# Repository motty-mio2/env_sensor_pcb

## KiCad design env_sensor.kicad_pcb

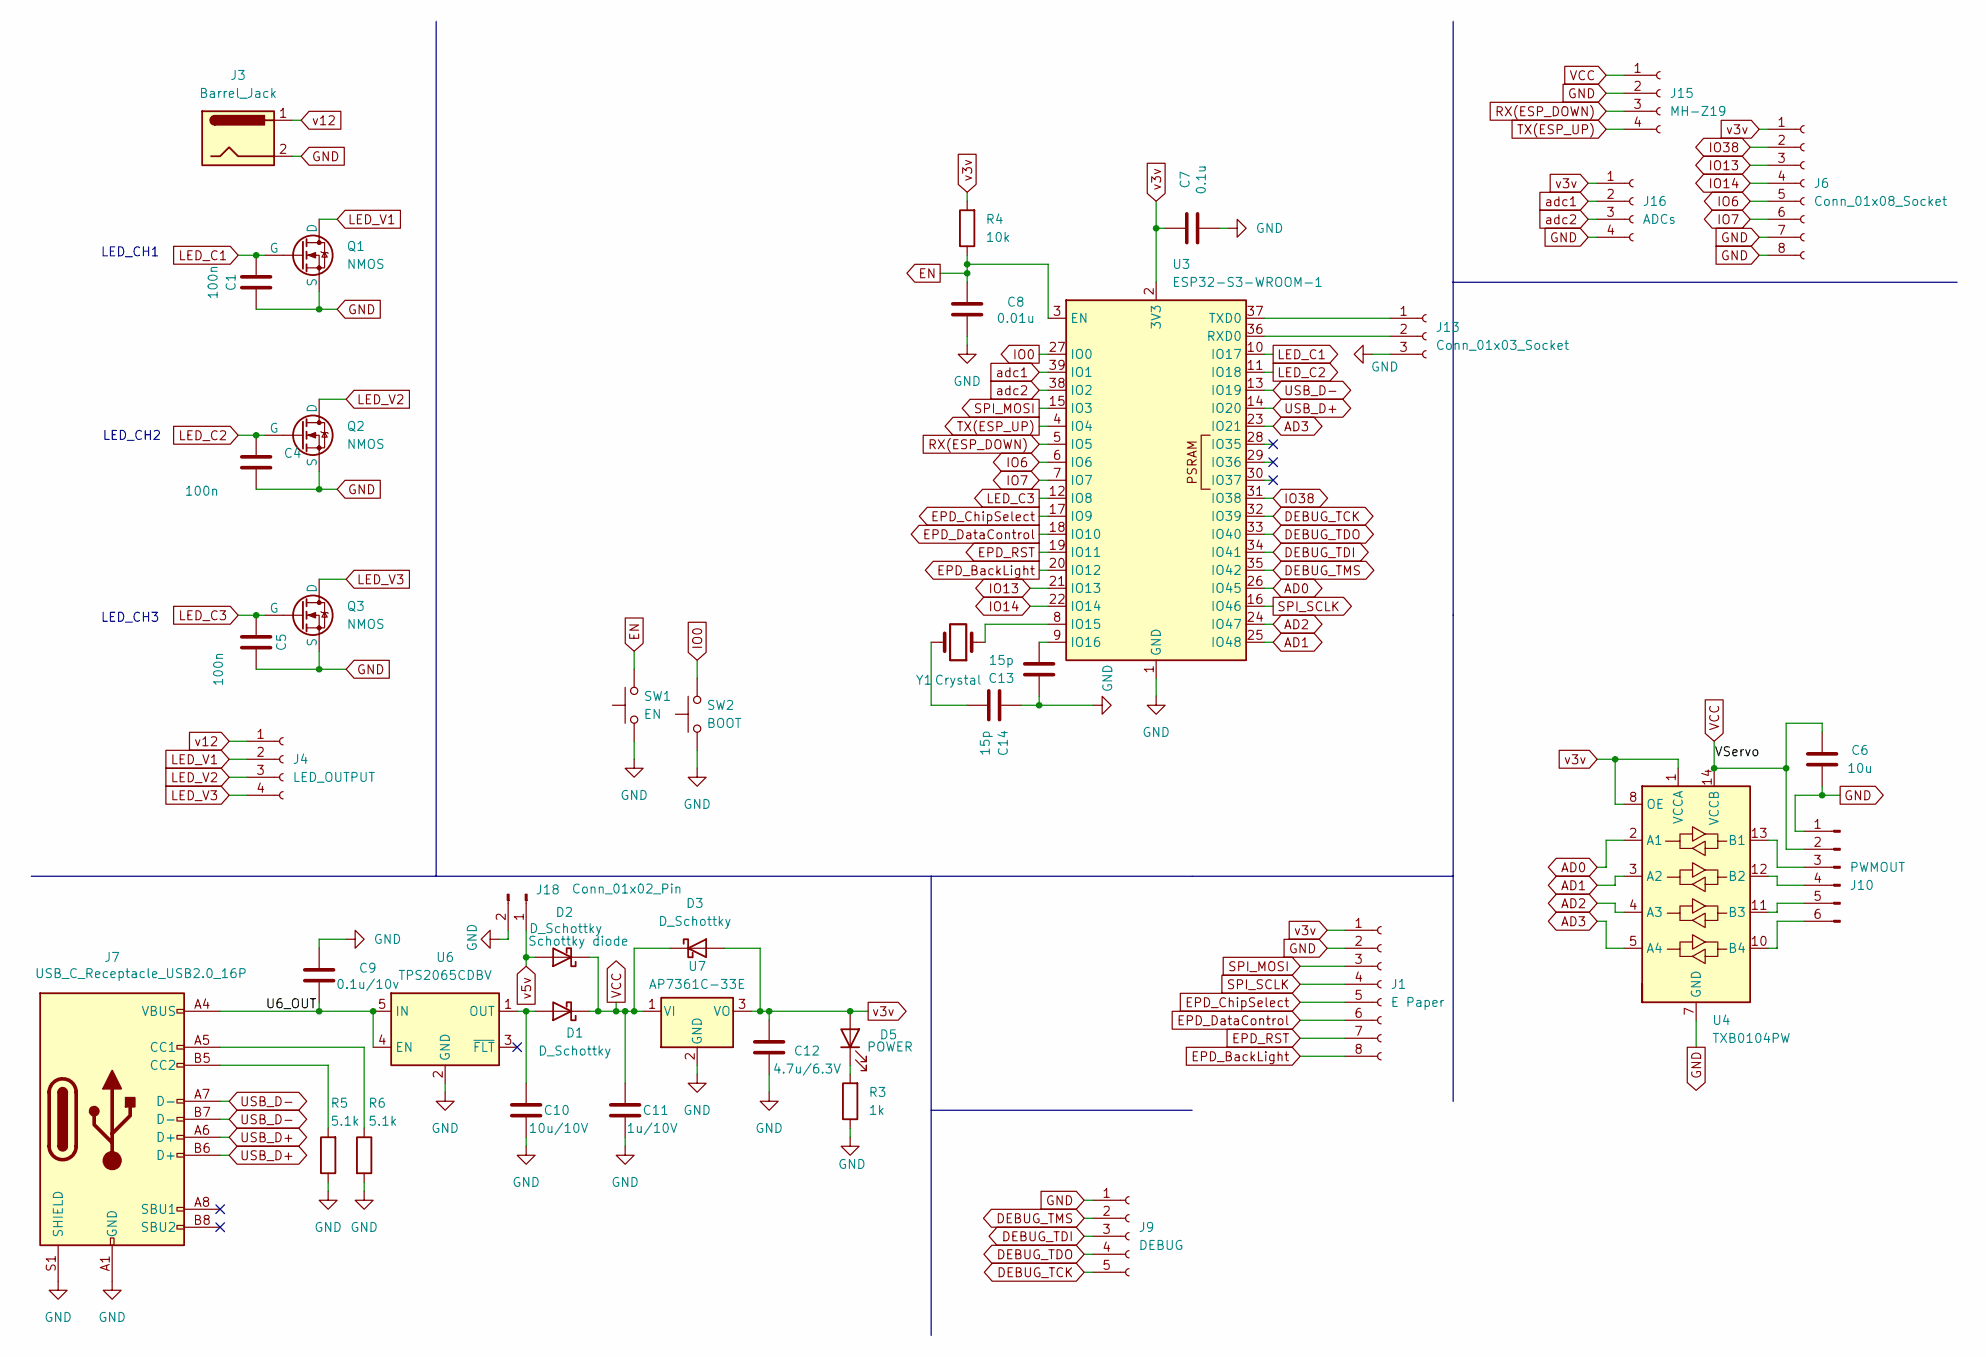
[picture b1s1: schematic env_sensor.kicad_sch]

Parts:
C1, C4, C5: 100n; C_0603_1608Metric; LCSC C14663
C6: 10u; C_0603_1608Metric; LCSC C19702
C7: 0.1u; C_0603_1608Metric; LCSC C14663
C8: 0.01u; C_0603_1608Metric; LCSC C57112
C9: 0.1u/10v; C_0603_1608Metric; LCSC C14663
C10: 10u/10V; C_0603_1608Metric; LCSC C19702
C11: 1u/10V; C_0603_1608Metric; LCSC C15849
C12: 4.7u/6.3V; C_0603_1608Metric; LCSC C19666
C13, C14: 15p; C_0603_1608Metric; LCSC C1644
D1, D2, D3: D_Schottky; D_SMA; LCSC C123070
D5: POWER; LED_0603_1608Metric; LCSC C2286
J1: E Paper; PinSocket_1x08_P2.54mm_Vertical
J3: Barrel_Jack; BarrelJack_GCT_DCJ200-10-A_Horizontal
J4: LED_OUTPUT; PinHeader_1x04_P2.54mm_Vertical
J6: Conn_01x08_Socket; PinSocket_2x04_P2.54mm_Vertical
J7: USB_C_Receptacle_USB2.0_16P; USB_C_Receptacle_GCT_USB4085; LCSC C7095263
J9: DEBUG; PinHeader_1x05_P2.54mm_Vertical
J10: PWMOUT; PinHeader_1x06_P2.54mm_Vertical
J13: Conn_01x03_Socket; PinHeader_1x03_P2.54mm_Vertical
J15: MH-Z19; PinSocket_1x04_P2.54mm_Vertical
J16: ADCs; PinSocket_1x04_P2.54mm_Vertical
J18: Conn_01x02_Pin; PinHeader_1x02_P2.54mm_Vertical
Q1, Q2, Q3: NMOS; TO-252; LCSC C557932
R3: 1k; R_0603_1608Metric; LCSC C21190
R4: 10k; R_0603_1608Metric; LCSC C25804
R5, R6: 5.1k; R_0603_1608Metric; LCSC C23186
SW1: EN; TVAF06-A020B-R; LCSC C2844396
SW2: BOOT; TVAF06-A020B-R; LCSC C2844396
U3: ESP32-S3-WROOM-1
U4: TXB0104PW; TSSOP-14_4.4x5mm_P0.65mm; LCSC C60708
U6: TPS2065CDBV; SOT-23-5; LCSC C353882
U7: AP7361C-33E; SOT-223-3_TabPin2; LCSC C500795
Y1: Crystal; Crystal_SMD_3215-2Pin_3.2x1.5mm; LCSC C1669858

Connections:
/U6_OUT: C9.2, J7.A4 (VBUS), J7.A9 (VBUS), J7.B4 (VBUS), J7.B9 (VBUS), U6.4 (EN), U6.5 (IN)
AD0: U3.26 (IO45), U4.2 (A1)
AD1: U3.25 (IO48), U4.3 (A2)
AD2: U3.24 (IO47), U4.4 (A3)
AD3: U3.23 (IO21), U4.5 (A4)
DEBUG_TCK: J9.5, U3.32 (IO39)
DEBUG_TDI: J9.3, U3.34 (IO41)
DEBUG_TDO: J9.4, U3.33 (IO40)
DEBUG_TMS: J9.2, U3.35 (IO42)
EN: C8.1, R4.1, SW1.2, U3.3 (EN)
EPD_BackLight: J1.8, U3.20 (IO12)
EPD_ChipSelect: J1.5, U3.17 (IO9)
EPD_DataControl: J1.6, U3.18 (IO10)
EPD_RST: J1.7, U3.19 (IO11)
GND: C1.2, C4.1, C5.1, C6.2, C7.2, C8.2, C9.1, C10.2, C11.2, C12.2, C13.1, C14.1, J1.2, J3.2, J6.7, J6.8, J7.A1 (GND), J7.A12 (GND), J7.B1 (GND), J7.B12 (GND), J7.S1 (SHIELD), J9.1, J10.1, J13.3, J15.2, J16.4, J18.2, Q1.3 (S), Q2.3 (S), Q3.3 (S), R3.1, R5.1, R6.2, SW1.1, SW2.1, U3.1 (GND), U3.40 (GND), U3.41 (GND), U4.7 (GND), U6.2 (GND), U7.2 (GND)
IO0: SW2.2, U3.27 (IO0)
IO6: J6.5, U3.6 (IO6)
IO7: J6.6, U3.7 (IO7)
IO13: J6.3, U3.21 (IO13)
IO14: J6.4, U3.22 (IO14)
IO38: J6.2, U3.31 (IO38)
LED_C1: C1.1, Q1.2 (G), U3.10 (IO17)
LED_C2: C4.2, Q2.2 (G), U3.11 (IO18)
LED_C3: C5.2, Q3.2 (G), U3.12 (IO8)
LED_V1: J4.2, Q1.1 (D)
LED_V2: J4.3, Q2.1 (D)
LED_V3: J4.4, Q3.1 (D)
unnamed: C14.2, Y1.2
unnamed: C10.1, D1.2 (A), U6.1 (OUT)
unnamed: D5.1 (K), R3.2
unnamed: J7.A5 (CC1), R6.1
unnamed: J7.B5 (CC2), R5.2
unnamed: J10.3, U4.13 (B1)
unnamed: J10.4, U4.12 (B2)
unnamed: J10.5, U4.11 (B3)
unnamed: J10.6, U4.10 (B4)
unnamed: J13.1, U3.37 (TXD0)
unnamed: J13.2, U3.36 (RXD0)
unnamed: U3.8 (IO15), Y1.1
unnamed: C13.2, U3.9 (IO16)
RX(ESP_DOWN): J15.3, U3.5 (IO5)
SPI_MOSI: J1.3, U3.15 (IO3)
SPI_SCLK: J1.4, U3.16 (IO46)
TX(ESP_UP): J15.4, U3.4 (IO4)
USB_D+: J7.A6 (D+), J7.B6 (D+), U3.14 (IO20)
USB_D-: J7.A7 (D-), J7.B7 (D-), U3.13 (IO19)
VCC: C6.1, C11.1, D1.1 (K), D2.1 (K), D3.1 (K), J10.2, J15.1, U4.14 (VCCB), U7.1 (VI)
adc1: J16.2, U3.39 (IO1)
adc2: J16.3, U3.38 (IO2)
v3v: C7.1, C12.1, D3.2 (A), D5.2 (A), J1.1, J6.1, J16.1, R4.2, U3.2 (3V3), U4.1 (VCCA), U4.8 (OE), U7.3 (VO)
v5v: D2.2 (A), J18.1
v12: J3.1, J4.1

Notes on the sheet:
LED_CH2
LED_CH1
LED_CH3

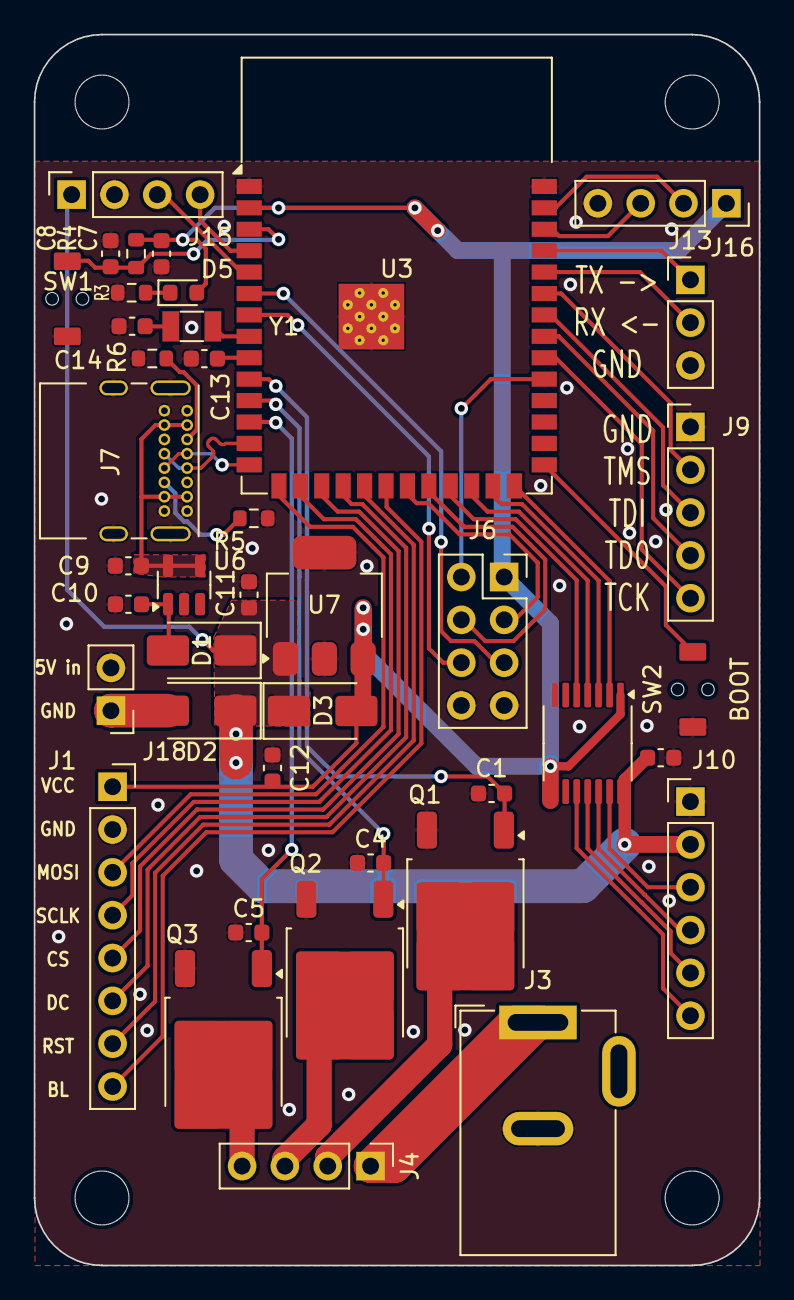
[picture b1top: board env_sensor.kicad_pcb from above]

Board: 2 copper layers, 43.0 x 73.0 mm, 41 parts (0 on the bottom side), 52 nets.

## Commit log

2024-08-07 env sensor init
2024-08-10 update MOS
2024-08-12 add drv8847 (Working)
2024-08-13 add motor drivers
2024-08-15 update lib
2024-08-15 update pcb
2024-08-16 update bom
2024-08-18 add esp32_s3
2024-09-08 add mh-z19 lib
2024-09-21 update lib for switch and fix DRCs
